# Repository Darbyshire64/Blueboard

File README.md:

# Blueboard
A Custom ANSI 109 Keyboard. Featuring:   
  - .91inch OLED display
  - Two Potentiomiters
  - 5 Macro Keys

https://blueprint.hackclub.com/projects/1084

## Important Notes About this project
 - If a Component is listed as $0.00 it is already owned by me
 - The BOM says RP2040 But the Schematics say ESP-32 C3 this is because i change mcu mid project however the xiao modules pinout are identical.
 - My Journal.md is outdated but the one on the blueprint project is up todate. the bot seemed to stop updating it automaticly.

### BOM
Alot of these components i or a freind has so i dont need to buy them and i can print the  case my self.

-----------------------------------------
| PRICE | QTY | ITEM              |LINK |
|-------|-----|-------------------|-----|
| $0.00 | x1  |XIAO RP2040        |     |
| $0.00 | x2  |MCP23017 GPIO Expander (SPDIP) | |
| $0.00 | x109| 1N2007 (DO-35    | |
| $0.00 | x2  |Rotary Encoder Switches| |
| $0.00 | x1  |.91inch OLED       |     |
|-------|-----|--Case-------------|-----|
| $0.00 | x1  |3D Printed Case    |     |
|------|------|--Key's-------------|-----|
| $24.00| x1  | Key Cap Set       | <a href="https://www.aliexpress.com/item/1005007817761888.html?spm=a2g0o.productlist.main.22.46c5788eAlocc4&algo_pvid=6bfc7eba-8c23-4d8e-acff-ef4339698735&algo_exp_id=6bfc7eba-8c23-4d8e-acff-ef4339698735-21&pdp_ext_f=%7B%22order%22%3A%226%22%2C%22eval%22%3A%221%22%2C%22fromPage%22%3A%22search%22%7D&pdp_npi=6%40dis%21GBP%2120.49%2120.49%21%21%2126.52%2126.52%21%402103834817615696840777362eceeb%2112000042316060294%21sea%21UK%210%21ABX%211%210%21n_tag%3A-29910%3Bd%3A9022af12%3Bm03_new_user%3A-29895&curPageLogUid=6jgkASDIeQmP&utparam-url=scene%3Asearch%7Cquery_from%3A%7Cx_object_id%3A1005007817761888%7C_p_origin_prod%3A£"> LINK </a> |
| $16.20| x109 | Switches          |<a href="https://www.aliexpress.com/item/1005002378701948.html?spm=a2g0o.productlist.main.2.57b657a07TkDOW&algo_pvid=97b4824a-0a2a-4a95-87c6-16175c94739a&algo_exp_id=97b4824a-0a2a-4a95-87c6-16175c94739a-1&pdp_ext_f=%7B%22order%22%3A%221849%22%2C%22eval%22%3A%221%22%2C%22fromPage%22%3A%22search%22%7D&pdp_npi=6%40dis%21USD%212.63%210.99%21%21%212.63%210.99%21%40211b65de17629907681648156ef251%2112000020915533413%21sea%21UK%210%21ABX%211%210%21n_tag%3A-29910%3Bd%3A9022af12%3Bm03_new_user%3A-29895%3BpisId%3A5000000190273873&curPageLogUid=0IDCmPXkWz1a&utparam-url=scene%3Asearch%7Cquery_from%3A%7Cx_object_id%3A1005002378701948%7C_p_origin_prod%3A#nav-specification">LINK </a> |
|$3.68  | x1   | Key Stabalizers Set  | <a href="https://www.aliexpress.com/item/1005004229140548.html?spm=a2g0o.productlist.main.29.7902rfnXrfnXtu&algo_pvid=2fd3785e-ad6c-4d89-9afd-bb18c151fe01&algo_exp_id=2fd3785e-ad6c-4d89-9afd-bb18c151fe01-26&pdp_ext_f=%7B%22order%22%3A%2238%22%2C%22eval%22%3A%221%22%2C%22fromPage%22%3A%22search%22%7D&pdp_npi=6%40dis%21USD%216.18%213.68%21%21%216.18%213.68%21%40211b61d017629911662487438e114c%2112000028456713257%21sea%21UK%210%21ABX%211%210%21n_tag%3A-29910%3Bd%3A9022af12%3Bm03_new_user%3A-29895%3BpisId%3A5000000190273874&curPageLogUid=07ZDBuWAGHXZ&utparam-url=scene%3Asearch%7Cquery_from%3A%7Cx_object_id%3A1005004229140548%7C_p_origin_prod%3A"> LINK </a>      |
|-------|------| PCB COSTS --------|------|
|$33.40 | x1   | PCB               |      |
|$18.63 | x1   | GSDL SHIPING      |      |
|-$20   |      | BP Coupon         |       |
|-------|------|-------------------|------|
| $75.91 |    | TOTAL With Coupon|      |
| $95.91 |     | TOTAL Without Coupon|      |

## Renders

## Case

## PCB

## Themeing

Blueboard is Themed and designed to my specific Liking. It features a Blue, Black and Brown Colour scheme. With a Zero RGB Aproach.

#### <a href="https://www.aliexpress.com/item/1005007817761888.html?spm=a2g0o.productlist.main.22.46c5788eAlocc4&algo_pvid=6bfc7eba-8c23-4d8e-acff-ef4339698735&algo_exp_id=6bfc7eba-8c23-4d8e-acff-ef4339698735-21&pdp_ext_f=%7B%22order%22%3A%226%22%2C%22eval%22%3A%221%22%2C%22fromPage%22%3A%22search%22%7D&pdp_npi=6%40dis%21GBP%2120.49%2120.49%21%21%2126.52%2126.52%21%402103834817615696840777362eceeb%2112000042316060294%21sea%21UK%210%21ABX%211%210%21n_tag%3A-29910%3Bd%3A9022af12%3Bm03_new_user%3A-29895&curPageLogUid=6jgkASDIeQmP&utparam-url=scene%3Asearch%7Cquery_from%3A%7Cx_object_id%3A1005007817761888%7C_p_origin_prod%3A"> Keycaps </a>

#### <a href="https://www.keyboard-layout-editor.com/##@_name=Blueboard&author=Lawri%20Darbyshire&switchMount=cherry&switchBrand=cherry&switchType=MX1A-21xx&pcb:true&plate:true%3B&@_x:1.5&c=%232b2b2b&t=%23ab8649%3B&=Esc&_x:1&c=%231c3b94%3B&=F1&=F2&=F3&=F4&_x:0.5&c=%232b2b2b%3B&=F5&=F6&=F7&=F8&_x:0.5&c=%231c3b94%3B&=F9&=F10&=F11&=F12&_x:0.25&c=%232b2b2b%3B&=PrtSc&=Scroll%20Lock&=Pause%0ABreak%3B&@_y:0.5&x:0.25&c=%23cccccc&t=%23000000&a:7%3B&=&_x:0.25&c=%231c3b94&t=%23ab8649&a:4%3B&=~%0A%60&=!%0A1&=%2F@%0A2&=%23%0A3&=$%0A4&=%25%0A5&=%5E%0A6&=%2F&%0A7&=*%0A8&=(%0A9&=)%0A0&=%2F_%0A-&=+%0A%2F=&_c=%232b2b2b&w:2%3B&=Backspace&_x:0.25%3B&=Insert&=Home&=PgUp&_x:0.25%3B&=Num%20Lock&=%2F%2F&=*&=-%3B&@_x:0.25&c=%23cccccc&t=%23000000&a:7%3B&=&_x:0.25&c=%232b2b2b&t=%23ab8649&a:4&w:1.5%3B&=Tab&_c=%231c3b94%3B&=Q&=W&=E&=R&=T&=Y&=U&=I&=O&=P&=%7B%0A%5B&=%7D%0A%5D&_w:1.5%3B&=%7C%0A%5C&_x:0.25&c=%232b2b2b%3B&=Delete&=End&=PgDn&_x:0.25&c=%231c3b94%3B&=7%0AHome&=8%0A%E2%86%91&=9%0APgUp&_c=%232b2b2b&h:2%3B&=+%3B&@_x:0.25&c=%23cccccc&t=%23000000&a:7%3B&=&_x:0.25&c=%232b2b2b&t=%23ab8649&a:4&w:1.75%3B&=Caps%20Lock&_c=%231c3b94%3B&=A&=S&=D&=F&=G&=H&=J&=K&=L&=%2F:%0A%2F%3B&=%22%0A'&_c=%23ab8649&t=%231c3b94&w:2.25%3B&=Enter&_x:3.5&c=%231c3b94&t=%23ab8649%3B&=4%0A%E2%86%90&=5&=6%0A%E2%86%92%3B&@_x:0.25&c=%23cccccc&t=%23000000&a:7%3B&=&_x:0.25&c=%232b2b2b&t=%23ab8649&a:4&w:2.25%3B&=Shift&_c=%231c3b94%3B&=Z&=X&=C&=V&=B&=N&=M&=%3C%0A,&=%3E%0A.&=%3F%0A%2F%2F&_c=%232b2b2b&w:2.75%3B&=Shift&_x:1.25&c=%23ab8649&t=%231c3b94%3B&=%E2%86%91&_x:1.25&c=%231c3b94&t=%23ab8649%3B&=1%0AEnd&=2%0A%E2%86%93&=3%0APgDn&_c=%23ab8649&t=%231c3b94&h:2%3B&=Enter%3B&@_x:0.25&c=%23cccccc&t=%23000000&a:7%3B&=&_x:0.25&c=%232b2b2b&t=%23ab8649&a:4&w:1.25%3B&=Ctrl&_w:1.25%3B&=Win&_w:1.25%3B&=Alt&_c=%23ab8649&t=%231c3b94&a:7&w:6.25%3B&=&_c=%232b2b2b&t=%23ab8649&a:4&w:1.25%3B&=Alt&_w:1.25%3B&=Win&_w:1.25%3B&=Menu&_w:1.25%3B&=Ctrl&_x:0.25&c=%23ab8649&t=%231c3b94%3B&=%E2%86%90&=%E2%86%93&=%E2%86%92&_x:0.25&c=%231c3b94&t=%23ab8649&w:2%3B&=0%0AIns&=.%0ADel"> Key Layout </a> 

## To Do
  - [X] PCB
    - [X] Deisign Schematic
      - [X] Switches
      - [X] RGB
      - [X] OLED
      - [X] Potentomiters
      - [X] MCU
      - [X] GPIO Expander 
    - [X] Design PCB
    - [X] Add Artwork
  - [ ] Export BOM to CSV
  - [X] Design Case
  - [X] Complete BOM
  - [ ] Write Skeleton Firmware (KMK)

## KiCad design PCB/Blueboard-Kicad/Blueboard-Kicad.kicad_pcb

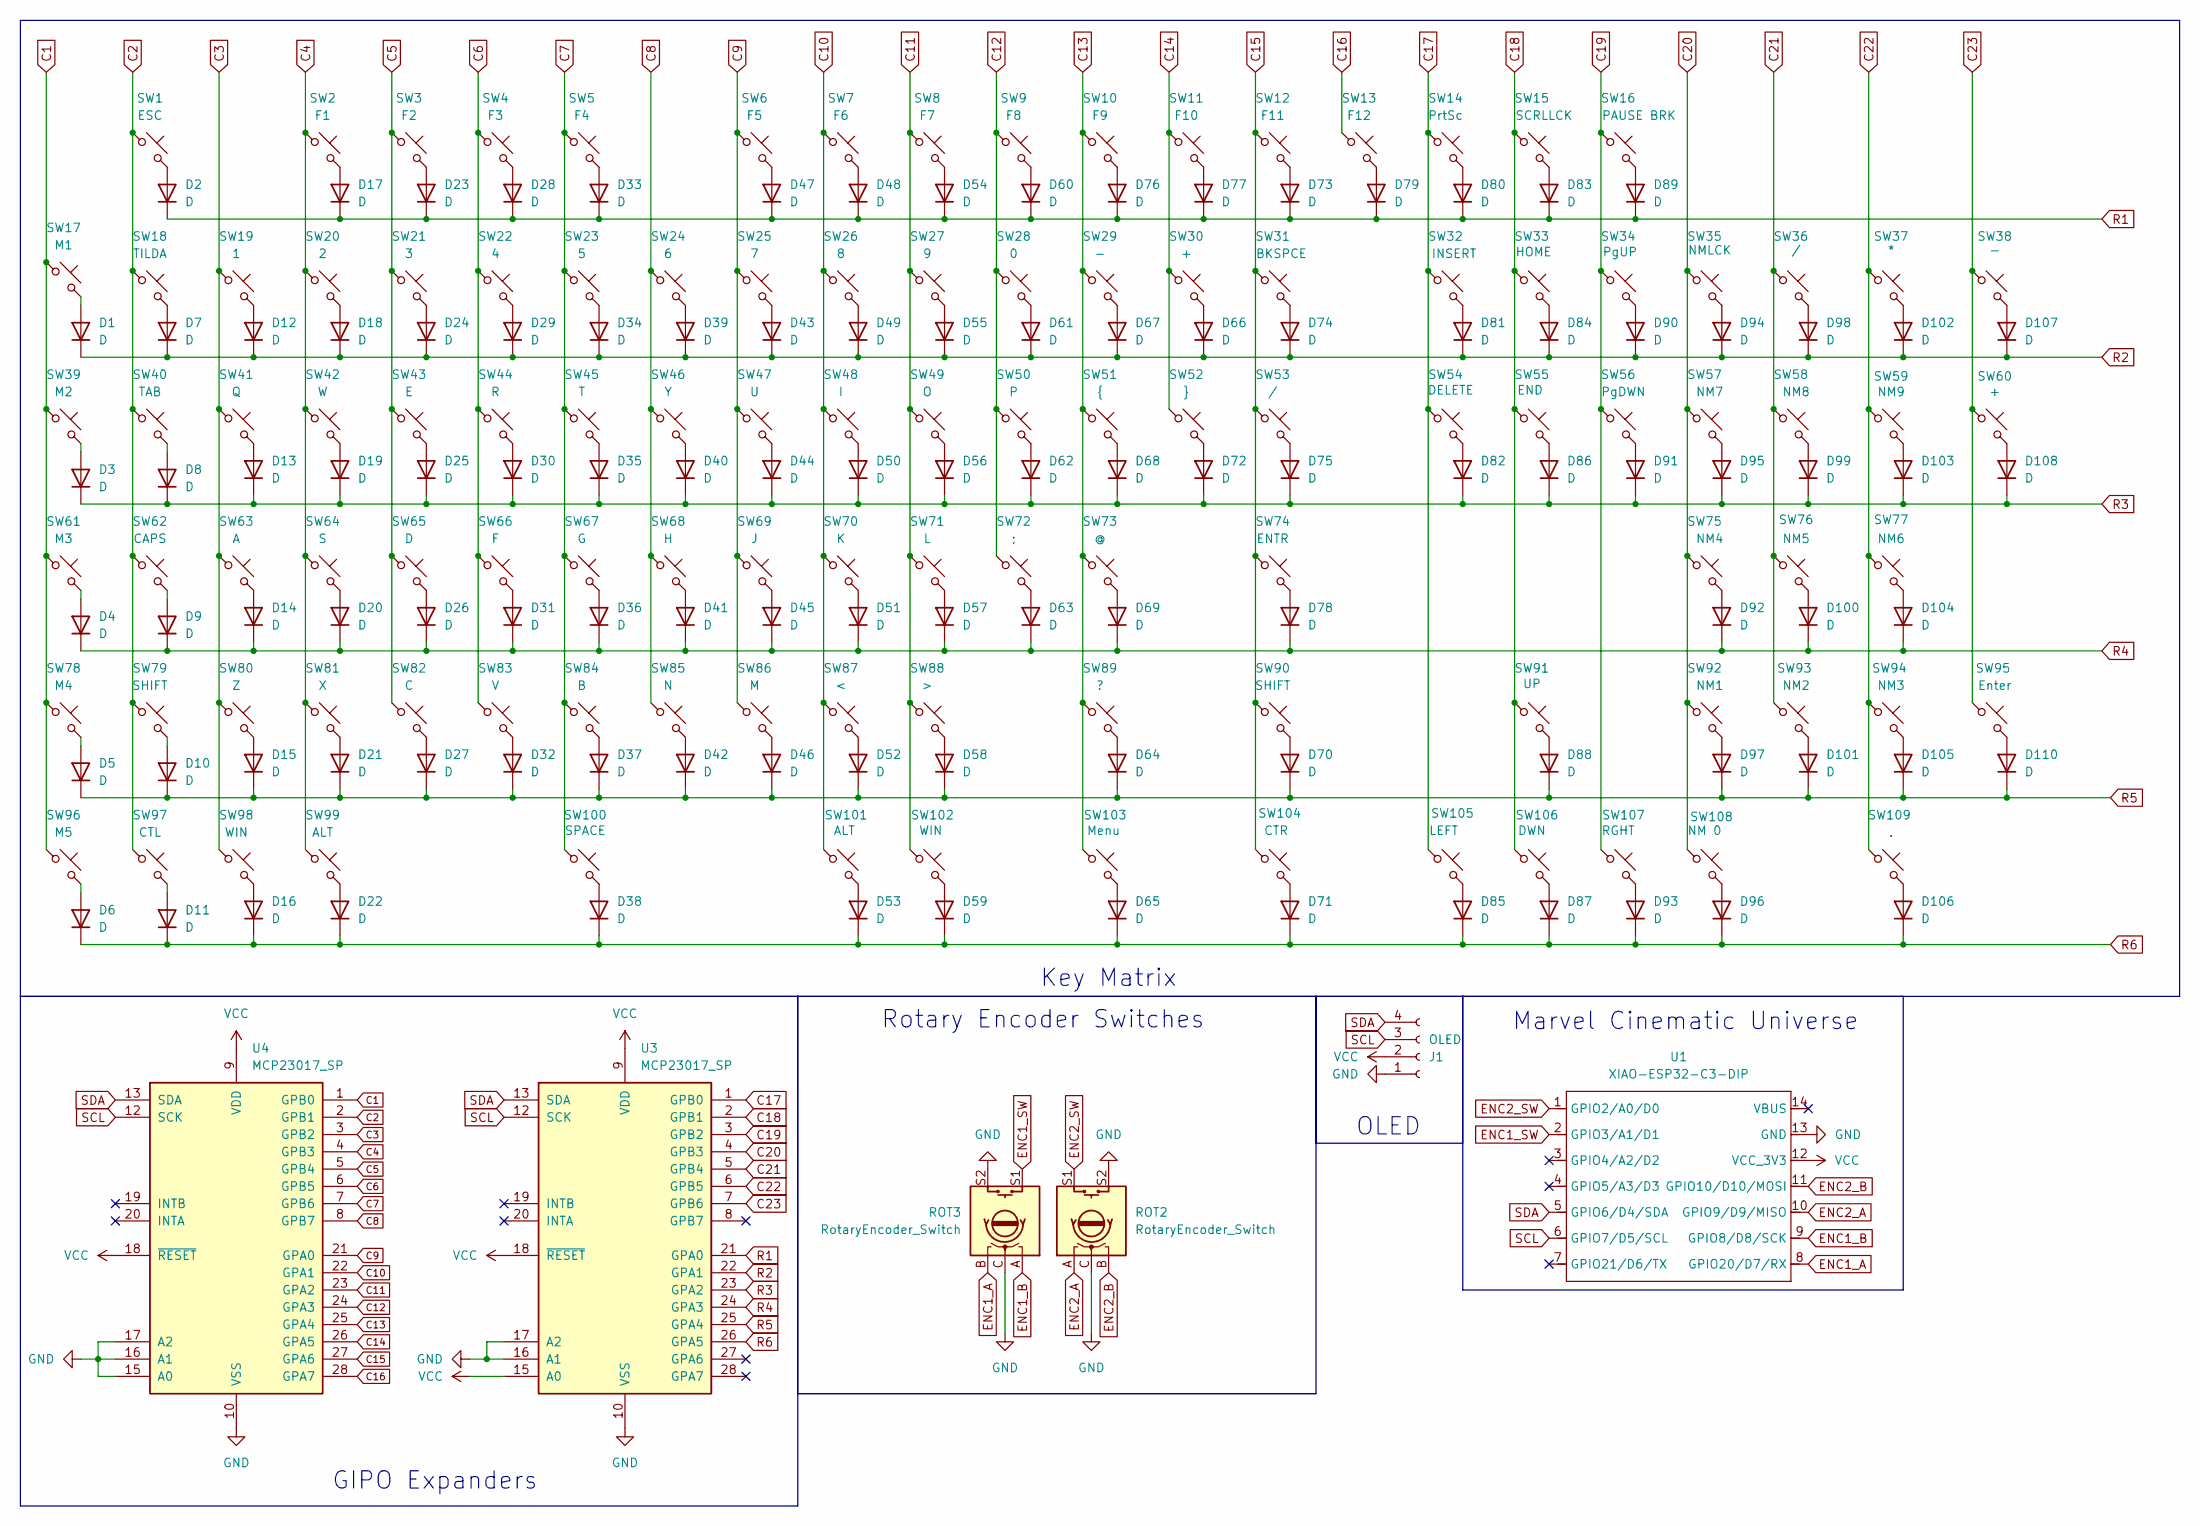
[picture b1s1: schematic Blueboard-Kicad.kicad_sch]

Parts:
D1, D2, D3, D4, D5, D6, D7, D8, D9, D10, D11, D12, D13, D14, D15, D16, D17, D18, D19, D20, D21, D22, D23, D24, D25, D26, D27, D28, D29, D30, D31, D32, D33, D34, D35, D36, D37, D38, D39, D40, D41, D42, D43, D44, D45, D46, D47, D48, D49, D50, D51, D52, D53, D54, D55, D56, D57, D58, D59, D60, D61, D62, D63, D64, D65, D66, D67, D68, D69, D70, D71, D72, D73, D74, D75, D76, D77, D78, D79, D80, D81, D82, D83, D84, D85, D86, D87, D88, D89, D90, D91, D92, D93, D94, D95, D96, D97, D98, D99, D100, D101, D102, D103, D104, D105, D106, D107, D108, D110: D; D_DO-41_SOD81_P7.62mm_Horizontal
J1: OLED; SSD1306-0.91-OLED-4pin-128x32
ROT2, ROT3: RotaryEncoder_Switch; RotaryEncoder_Alps_EC11E-Switch_Vertical_H20mm_MountingHoles
SW1: ESC; SW_Cherry_MX1A_1.00u_PCB
SW2: F1; SW_Cherry_MX1A_1.00u_PCB
SW3: F2; SW_Cherry_MX1A_1.00u_PCB
SW4: F3; SW_Cherry_MX1A_1.00u_PCB
SW5: F4; SW_Cherry_MX1A_1.00u_PCB
SW6: F5; SW_Cherry_MX1A_1.00u_PCB
SW7: F6; SW_Cherry_MX1A_1.00u_PCB
SW8: F7; SW_Cherry_MX1A_1.00u_PCB
SW9: F8; SW_Cherry_MX1A_1.00u_PCB
SW10: F9; SW_Cherry_MX1A_1.00u_PCB
SW11: F10; SW_Cherry_MX1A_1.00u_PCB
SW12: F11; SW_Cherry_MX1A_1.25u_PCB
SW13: F12; SW_Cherry_MX1A_1.00u_PCB
SW14: PrtSc; SW_Cherry_MX1A_1.00u_PCB
SW15: SCRLLCK; SW_Cherry_MX1A_1.00u_PCB
SW16: PAUSE BRK; SW_Cherry_MX1A_1.00u_PCB
SW17: M1; SW_Cherry_MX1A_1.00u_PCB
SW18: TILDA; SW_Cherry_MX1A_1.00u_PCB
SW19: 1; SW_Cherry_MX1A_1.00u_PCB
SW20: 2; SW_Cherry_MX1A_1.00u_PCB
SW21: 3; SW_Cherry_MX1A_1.00u_PCB
SW22: 4; SW_Cherry_MX1A_1.00u_PCB
SW23: 5; SW_Cherry_MX1A_1.00u_PCB
SW24: 6; SW_Cherry_MX1A_1.00u_PCB
SW25: 7; SW_Cherry_MX1A_1.00u_PCB
SW26: 8; SW_Cherry_MX1A_1.00u_PCB
SW27: 9; SW_Cherry_MX1A_1.00u_PCB
SW28: 0; SW_Cherry_MX1A_1.00u_PCB
SW29, SW38: -; SW_Cherry_MX1A_1.00u_PCB
SW30: +; SW_Cherry_MX1A_1.00u_PCB
SW31: BKSPCE; SW_Cherry_MX1A_2.00u_PCB
SW32: INSERT; SW_Cherry_MX1A_1.00u_PCB
SW33: HOME; SW_Cherry_MX1A_1.00u_PCB
SW34: PgUP; SW_Cherry_MX1A_1.00u_PCB
SW35: NMLCK; SW_Cherry_MX1A_1.00u_PCB
SW36: /; SW_Cherry_MX1A_1.00u_PCB
SW37: *; SW_Cherry_MX1A_1.00u_PCB
SW39: M2; SW_Cherry_MX1A_1.00u_PCB
SW40: TAB; SW_Cherry_MX1A_1.50u_PCB
SW41: Q; SW_Cherry_MX1A_1.00u_PCB
SW42: W; SW_Cherry_MX1A_1.00u_PCB
SW43: E; SW_Cherry_MX1A_1.00u_PCB
SW44: R; SW_Cherry_MX1A_1.00u_PCB
SW45: T; SW_Cherry_MX1A_1.00u_PCB
SW46: Y; SW_Cherry_MX1A_1.00u_PCB
SW47: U; SW_Cherry_MX1A_1.00u_PCB
SW48: I; SW_Cherry_MX1A_1.00u_PCB
SW49: O; SW_Cherry_MX1A_1.00u_PCB
SW50: P; SW_Cherry_MX1A_1.00u_PCB
SW51: {; SW_Cherry_MX1A_1.00u_PCB
SW52: }; SW_Cherry_MX1A_1.00u_PCB
SW53: /; SW_Cherry_MX1A_1.25u_PCB
SW54: DELETE; SW_Cherry_MX1A_1.00u_PCB
SW55: END; SW_Cherry_MX1A_1.00u_PCB
SW56: PgDWN; SW_Cherry_MX1A_1.00u_PCB
SW57: NM7; SW_Cherry_MX1A_1.00u_PCB
SW58: NM8; SW_Cherry_MX1A_1.00u_PCB
SW59: NM9; SW_Cherry_MX1A_1.00u_PCB
SW60: +; SW_Cherry_MX1A_2.00u_Vertical_PCB
SW61: M3; SW_Cherry_MX1A_1.00u_PCB
SW62: CAPS; SW_Cherry_MX1A_1.75u_PCB
SW63: A; SW_Cherry_MX1A_1.00u_PCB
SW64: S; SW_Cherry_MX1A_1.00u_PCB
SW65: D; SW_Cherry_MX1A_1.00u_PCB
SW66: F; SW_Cherry_MX1A_1.00u_PCB
SW67: G; SW_Cherry_MX1A_1.00u_PCB
SW68: H; SW_Cherry_MX1A_1.00u_PCB
SW69: J; SW_Cherry_MX1A_1.00u_PCB
SW70: K; SW_Cherry_MX1A_1.00u_PCB
SW71: L; SW_Cherry_MX1A_1.00u_PCB
SW72: ;; SW_Cherry_MX1A_1.00u_PCB
SW73: @; SW_Cherry_MX1A_1.00u_PCB
SW74: ENTR; SW_Cherry_MX1A_2.25u_PCB
SW75: NM4; SW_Cherry_MX1A_1.00u_PCB
SW76: NM5; SW_Cherry_MX1A_1.00u_PCB
SW77: NM6; SW_Cherry_MX1A_1.00u_PCB
SW78: M4; SW_Cherry_MX1A_1.00u_PCB
SW79: SHIFT; SW_Cherry_MX1A_2.25u_PCB
SW80: Z; SW_Cherry_MX1A_1.00u_PCB
SW81: X; SW_Cherry_MX1A_1.00u_PCB
SW82: C; SW_Cherry_MX1A_1.00u_PCB
SW83: V; SW_Cherry_MX1A_1.00u_PCB
SW84: B; SW_Cherry_MX1A_1.00u_PCB
SW85: N; SW_Cherry_MX1A_1.00u_PCB
SW86: M; SW_Cherry_MX1A_1.00u_PCB
SW87: <; SW_Cherry_MX1A_1.00u_PCB
SW88: >; SW_Cherry_MX1A_1.00u_PCB
SW89: ?; SW_Cherry_MX1A_1.00u_PCB
SW90: SHIFT; SW_Cherry_MX1A_2.75u_PCB
SW91: UP; SW_Cherry_MX1A_1.00u_PCB
SW92: NM1; SW_Cherry_MX1A_1.00u_PCB
SW93: NM2; SW_Cherry_MX1A_1.00u_PCB
SW94: NM3; SW_Cherry_MX1A_1.00u_PCB
SW95: Enter; SW_Cherry_MX1A_2.00u_Vertical_PCB
SW96: M5; SW_Cherry_MX1A_1.00u_PCB
SW97: CTL; SW_Cherry_MX1A_1.25u_PCB
SW98, SW102: WIN; SW_Cherry_MX1A_1.25u_PCB
SW99, SW101: ALT; SW_Cherry_MX1A_1.25u_PCB
SW100: SPACE; SW_Cherry_MX1A_6.25u_PCB
SW103: Menu; SW_Cherry_MX1A_1.25u_PCB
SW104: CTR; SW_Cherry_MX1A_1.25u_PCB
SW105: LEFT; SW_Cherry_MX1A_1.00u_PCB
SW106: DWN; SW_Cherry_MX1A_1.00u_PCB
SW107: RGHT; SW_Cherry_MX1A_1.00u_PCB
SW108: NM 0; SW_Cherry_MX1A_2.00u_PCB
SW109: .; SW_Cherry_MX1A_1.00u_PCB
U1: XIAO-ESP32-C3-DIP; XIAO-ESP32C3-DIP
U3, U4: MCP23017_SP; DIP-28_W7.62mm

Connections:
C1: SW17.1, SW39.1, SW61.1, SW78.1, SW96.1, U4.1 (GPB0)
C2: SW1.1, SW18.1, SW40.1, SW62.1, SW79.1, SW97.1, U4.2 (GPB1)
C3: SW19.1, SW41.1, SW63.1, SW80.1, SW98.1, U4.3 (GPB2)
C4: SW2.1, SW20.1, SW42.1, SW64.1, SW81.1, SW99.1, U4.4 (GPB3)
C5: SW3.1, SW21.1, SW43.1, SW65.1, SW82.1, U4.5 (GPB4)
C6: SW4.1, SW22.1, SW44.1, SW66.1, SW83.1, U4.6 (GPB5)
C7: SW5.1, SW23.1, SW45.1, SW67.1, SW84.1, SW100.1, U4.7 (GPB6)
C8: SW24.1, SW46.1, SW68.1, SW85.1, U4.8 (GPB7)
C9: SW6.1, SW25.1, SW47.1, SW69.1, SW86.1, U4.21 (GPA0)
C10: SW7.1, SW26.1, SW48.1, SW70.1, SW87.1, SW101.1, U4.22 (GPA1)
C11: SW8.1, SW27.1, SW49.1, SW71.1, SW88.1, SW102.1, U4.23 (GPA2)
C12: SW9.1, SW28.1, SW50.1, SW72.1, U4.24 (GPA3)
C13: SW10.1, SW29.1, SW51.1, SW73.1, SW89.1, SW103.1, U4.25 (GPA4)
C14: SW11.1, SW30.1, SW52.1, U4.26 (GPA5)
C15: SW12.1, SW31.1, SW53.1, SW74.1, SW90.1, SW104.1, U4.27 (GPA6)
C16: SW13.1, U4.28 (GPA7)
C17: SW14.1, SW32.1, SW54.1, SW105.1, U3.1 (GPB0)
C18: SW15.1, SW33.1, SW55.1, SW91.1, SW106.1, U3.2 (GPB1)
C19: SW16.1, SW34.1, SW56.1, SW107.1, U3.3 (GPB2)
C20: SW35.1, SW57.1, SW75.1, SW92.1, SW108.1, U3.4 (GPB3)
C21: SW36.1, SW58.1, SW76.1, SW93.1, U3.5 (GPB4)
C22: SW37.1, SW59.1, SW77.1, SW94.1, SW109.1, U3.6 (GPB5)
C23: SW38.1, SW60.1, SW95.1, U3.7 (GPB6)
ENC1_A: ROT3.B, U1.8 (GPIO20/D7/RX)
ENC1_B: ROT3.A, U1.9 (GPIO8/D8/SCK)
ENC1_SW: ROT3.S1, U1.2 (GPIO3/A1/D1)
ENC2_A: ROT2.A, U1.10 (GPIO9/D9/MISO)
ENC2_B: ROT2.B, U1.11 (GPIO10/D10/MOSI)
ENC2_SW: ROT2.S1, U1.1 (GPIO2/A0/D0)
GND: J1.1, ROT2.C, ROT2.S2, ROT3.C, ROT3.S2, U1.13 (GND), U3.10 (VSS), U3.16 (A1), U3.17 (A2), U4.10 (VSS), U4.15 (A0), U4.16 (A1), U4.17 (A2)
unnamed: D1.2 (A), SW17.2
unnamed: D2.2 (A), SW1.2
unnamed: D3.2 (A), SW39.2
unnamed: D4.2 (A), SW61.2
unnamed: D5.2 (A), SW78.2
unnamed: D6.2 (A), SW96.2
unnamed: D7.2 (A), SW18.2
unnamed: D8.2 (A), SW40.2
unnamed: D9.2 (A), SW62.2
unnamed: D10.2 (A), SW79.2
unnamed: D11.2 (A), SW97.2
unnamed: D12.2 (A), SW19.2
unnamed: D13.2 (A), SW41.2
unnamed: D14.2 (A), SW63.2
unnamed: D15.2 (A), SW80.2
unnamed: D16.2 (A), SW98.2
unnamed: D17.2 (A), SW2.2
unnamed: D18.2 (A), SW20.2
unnamed: D19.2 (A), SW42.2
unnamed: D20.2 (A), SW64.2
unnamed: D21.2 (A), SW81.2
unnamed: D22.2 (A), SW99.2
unnamed: D23.2 (A), SW3.2
unnamed: D24.2 (A), SW21.2
unnamed: D25.2 (A), SW43.2
unnamed: D26.2 (A), SW65.2
unnamed: D27.2 (A), SW82.2
unnamed: D28.2 (A), SW4.2
unnamed: D29.2 (A), SW22.2
unnamed: D30.2 (A), SW44.2
unnamed: D31.2 (A), SW66.2
unnamed: D32.2 (A), SW83.2
unnamed: D33.2 (A), SW5.2
unnamed: D34.2 (A), SW23.2
unnamed: D35.2 (A), SW45.2
unnamed: D36.2 (A), SW67.2
unnamed: D37.2 (A), SW84.2
unnamed: D38.2 (A), SW100.2
unnamed: D39.2 (A), SW24.2
unnamed: D40.2 (A), SW46.2
unnamed: D41.2 (A), SW68.2
unnamed: D42.2 (A), SW85.2
unnamed: D43.2 (A), SW25.2
unnamed: D44.2 (A), SW47.2
unnamed: D45.2 (A), SW69.2
unnamed: D46.2 (A), SW86.2
unnamed: D47.2 (A), SW6.2
unnamed: D48.2 (A), SW7.2
unnamed: D49.2 (A), SW26.2
unnamed: D50.2 (A), SW48.2
unnamed: D51.2 (A), SW70.2
unnamed: D52.2 (A), SW87.2
unnamed: D53.2 (A), SW101.2
unnamed: D54.2 (A), SW8.2
unnamed: D55.2 (A), SW27.2
unnamed: D56.2 (A), SW49.2
unnamed: D57.2 (A), SW71.2
unnamed: D58.2 (A), SW88.2
unnamed: D59.2 (A), SW102.2
unnamed: D60.2 (A), SW9.2
unnamed: D61.2 (A), SW28.2
unnamed: D62.2 (A), SW50.2
unnamed: D63.2 (A), SW72.2
unnamed: D64.2 (A), SW89.2
unnamed: D65.2 (A), SW103.2
unnamed: D66.2 (A), SW30.2
unnamed: D67.2 (A), SW29.2
unnamed: D68.2 (A), SW51.2
unnamed: D69.2 (A), SW73.2
unnamed: D70.2 (A), SW90.2
unnamed: D71.2 (A), SW104.2
unnamed: D72.2 (A), SW52.2
unnamed: D73.2 (A), SW12.2
unnamed: D74.2 (A), SW31.2
unnamed: D75.2 (A), SW53.2
unnamed: D76.2 (A), SW10.2
unnamed: D77.2 (A), SW11.2
unnamed: D78.2 (A), SW74.2
unnamed: D79.2 (A), SW13.2
unnamed: D80.2 (A), SW14.2
unnamed: D81.2 (A), SW32.2
unnamed: D82.2 (A), SW54.2
unnamed: D83.2 (A), SW15.2
unnamed: D84.2 (A), SW33.2
unnamed: D85.2 (A), SW105.2
unnamed: D86.2 (A), SW55.2
unnamed: D87.2 (A), SW106.2
unnamed: D88.2 (A), SW91.2
unnamed: D89.2 (A), SW16.2
unnamed: D90.2 (A), SW34.2
unnamed: D91.2 (A), SW56.2
unnamed: D92.2 (A), SW75.2
unnamed: D93.2 (A), SW107.2
unnamed: D94.2 (A), SW35.2
unnamed: D95.2 (A), SW57.2
unnamed: D96.2 (A), SW108.2
unnamed: D97.2 (A), SW92.2
unnamed: D98.2 (A), SW36.2
unnamed: D99.2 (A), SW58.2
unnamed: D100.2 (A), SW76.2
unnamed: D101.2 (A), SW93.2
unnamed: D102.2 (A), SW37.2
unnamed: D103.2 (A), SW59.2
unnamed: D104.2 (A), SW77.2
unnamed: D105.2 (A), SW94.2
unnamed: D106.2 (A), SW109.2
unnamed: D107.2 (A), SW38.2
unnamed: D108.2 (A), SW60.2
unnamed: D110.2 (A), SW95.2
R1: D2.1 (K), D17.1 (K), D23.1 (K), D28.1 (K), D33.1 (K), D47.1 (K), D48.1 (K), D54.1 (K), D60.1 (K), D73.1 (K), D76.1 (K), D77.1 (K), D79.1 (K), D80.1 (K), D83.1 (K), D89.1 (K), U3.21 (GPA0)
R2: D1.1 (K), D7.1 (K), D12.1 (K), D18.1 (K), D24.1 (K), D29.1 (K), D34.1 (K), D39.1 (K), D43.1 (K), D49.1 (K), D55.1 (K), D61.1 (K), D66.1 (K), D67.1 (K), D74.1 (K), D81.1 (K), D84.1 (K), D90.1 (K), D94.1 (K), D98.1 (K), D102.1 (K), D107.1 (K), U3.22 (GPA1)
R3: D3.1 (K), D8.1 (K), D13.1 (K), D19.1 (K), D25.1 (K), D30.1 (K), D35.1 (K), D40.1 (K), D44.1 (K), D50.1 (K), D56.1 (K), D62.1 (K), D68.1 (K), D72.1 (K), D75.1 (K), D82.1 (K), D86.1 (K), D91.1 (K), D95.1 (K), D99.1 (K), D103.1 (K), D108.1 (K), U3.23 (GPA2)
R4: D4.1 (K), D9.1 (K), D14.1 (K), D20.1 (K), D26.1 (K), D31.1 (K), D36.1 (K), D41.1 (K), D45.1 (K), D51.1 (K), D57.1 (K), D63.1 (K), D69.1 (K), D78.1 (K), D92.1 (K), D100.1 (K), D104.1 (K), U3.24 (GPA3)
R5: D5.1 (K), D10.1 (K), D15.1 (K), D21.1 (K), D27.1 (K), D32.1 (K), D37.1 (K), D42.1 (K), D46.1 (K), D52.1 (K), D58.1 (K), D64.1 (K), D70.1 (K), D88.1 (K), D97.1 (K), D101.1 (K), D105.1 (K), D110.1 (K), U3.25 (GPA4)
R6: D6.1 (K), D11.1 (K), D16.1 (K), D22.1 (K), D38.1 (K), D53.1 (K), D59.1 (K), D65.1 (K), D71.1 (K), D85.1 (K), D87.1 (K), D93.1 (K), D96.1 (K), D106.1 (K), U3.26 (GPA5)
SCL: J1.3, U1.6 (GPIO7/D5/SCL), U3.12 (SCK), U4.12 (SCK)
SDA: J1.4, U1.5 (GPIO6/D4/SDA), U3.13 (SDA), U4.13 (SDA)
VCC: J1.2, U1.12 (VCC_3V3), U3.9 (VDD), U3.15 (A0), U3.18 (~RESET), U4.9 (VDD), U4.18 (~RESET)

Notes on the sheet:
Key Matrix
OLED
GIPO Expanders
Marvel Cinematic Universe
Rotary Encoder Switches

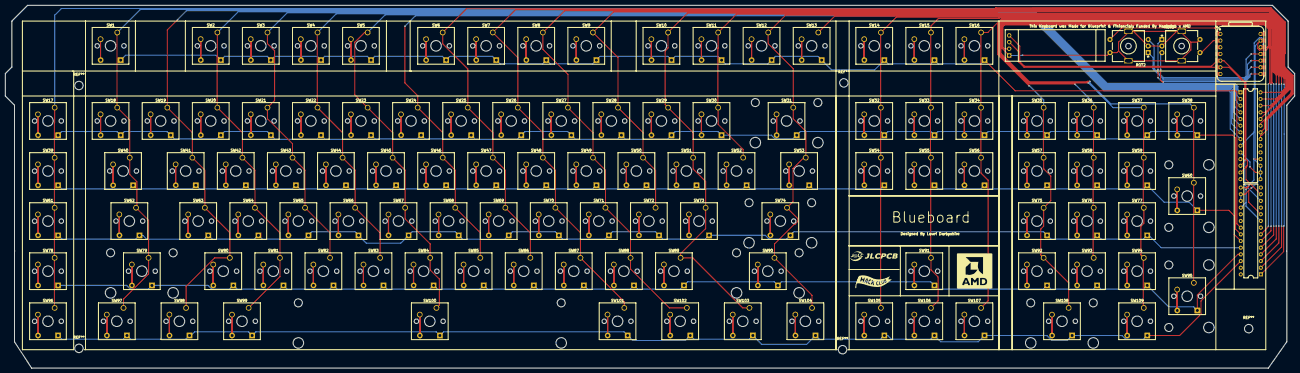
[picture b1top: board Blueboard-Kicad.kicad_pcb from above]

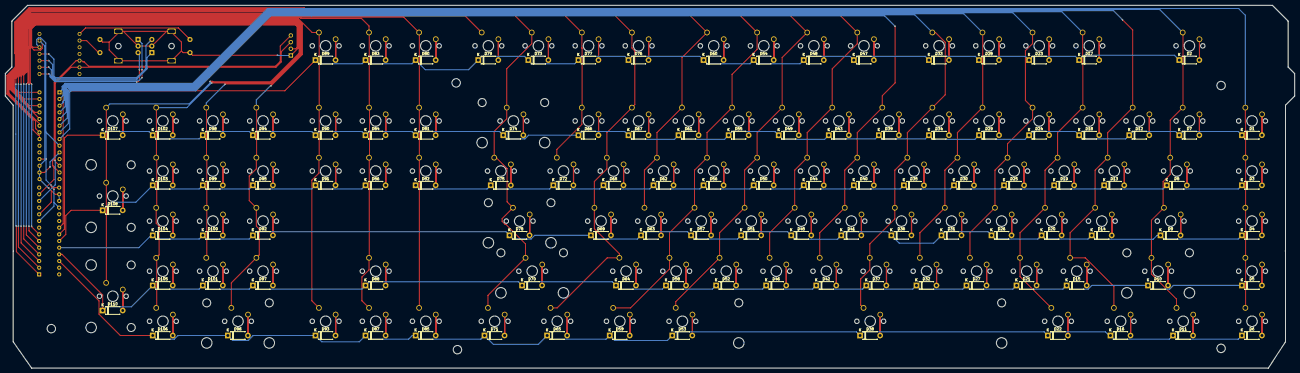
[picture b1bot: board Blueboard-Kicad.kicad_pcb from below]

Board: 2 copper layers, 490.5 x 138.0 mm, 224 parts (109 on the bottom side), 148 nets.

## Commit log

2025-10-27 Enhance README with keycaps and layout diagrams
    =
2025-10-27 Create Layout-WithPotOLED
2025-10-27 Rename Layout-WithPotOLED to Layout-WithPotOLED.json
2025-10-27 Add initial layout configuration
2025-10-27 Rename Layout to Layout.json
2025-10-27 Added New Image
    Added New image
2025-10-27 Create TEMP
2025-10-27 Added Images
2025-10-27 Completed Key Matrix
2025-10-28 Updated Schematic With Completed Matrix
2025-10-29 Finished Schematc + Layedout Components
2025-10-29 Started Adding the Diodes to the PCB
2025-11-05 Update To Do list with completed schematic tasks
2025-11-10 Made alot of changes to the PCB
2025-11-11 Finalized PCB
2025-11-13 Added BOM
    Added BOM
2025-11-13 Revise component prices and add stabilizers
    Updated prices and links for components in the README.
2025-11-13 Mark BOM as complete in README
2025-11-20 Update total cost and add BP coupon in README
2025-11-23 Forgot to Commit PCB Changes
2025-11-24 Add images
2025-11-24 Update keyboard model from ANSI 104 to ANSI 109
2025-11-24 Worked On Blender Render
2025-11-24 Added Renders to Readme
2025-11-24 Update README with project link and important notes
    Added important notes and a project link to the README.
2025-11-25 Started Firmware
2025-11-30 Redid a bit of the Firmware.
2025-11-30 Add BOM.csv
2025-11-30 Updated Firmware
2025-11-30 Reorganised Files and updated Gerber's & F3z file
2025-12-01 Changed Prices
    Changed Pricing
2025-12-01 Update shipping cost and total prices in README
2025-12-01 Revise BOM with updated prices and links
    Updated BOM.csv to reflect new pricing and item links.
